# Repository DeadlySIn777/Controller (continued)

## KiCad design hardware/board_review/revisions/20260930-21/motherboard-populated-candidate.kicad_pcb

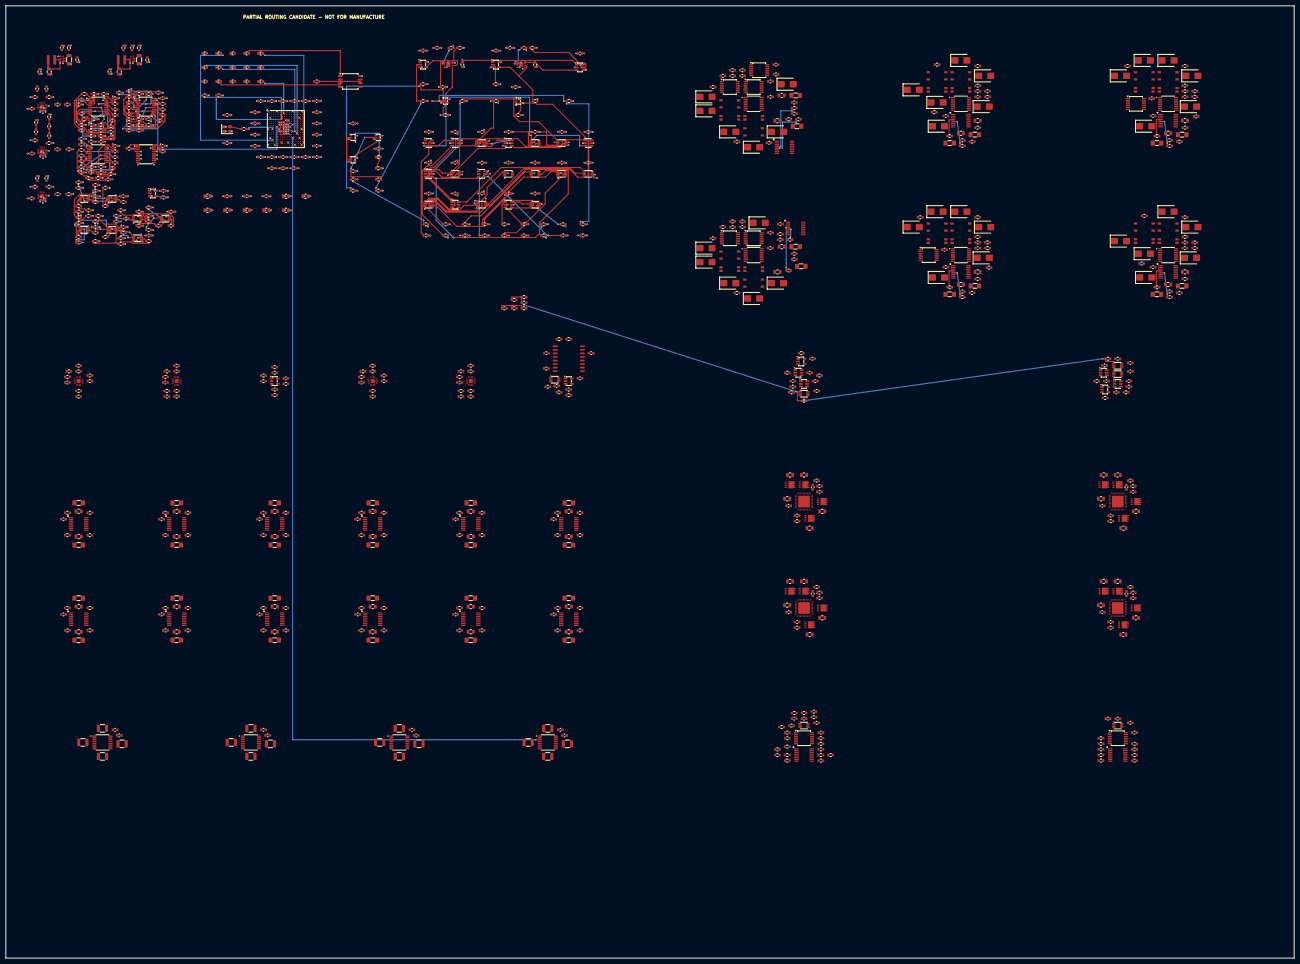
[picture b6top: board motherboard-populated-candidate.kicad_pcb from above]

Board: 6 copper layers, 460.0 x 340.0 mm, 880 parts (0 on the bottom side), 637 nets.

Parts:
C1001, C1002, C1003, C1004, C1005, C1006, C1007, C1008, C1009, C1010, C1011, C1012, C1013, C1014, C1015, C1016, C1017, C1018, C1019, C1020, C1021, C1022, C1023, C1035, C1038: 885012206046; C_0603_1608Metric
C1024, C1028, C1029, C1030, C1031, C1032, C1033, C1034: 885012207053; C_0805_2012Metric
C1025, C1026, C1027, C1036, C1039: 885012206052; C_0603_1608Metric
C1037: 885012206040; C_0603_1608Metric
C2001, C2004: C3216X7R1E106K160AB; C_1206_3216Metric
C2002, C2005: C2012X7S1A226M125AC; C_0805_2012Metric
C2003, C2006: GRM1885C1H682JA01D; C_0603_1608Metric
C2007, C2008, C2009, C2010, C3003, C3004, C3005, C3006, C3007, C3008, C3009, C4001, C4002, C4003, C4004, C4005, C4006, C4007, C4008, C4009, C4010, C4011, C4012, C4013, C4014, C4015, C4016, C4017, C4018, C4019, C5001, C5002, C5003, C5004, C5005, C5006, C5007, C5008, C5009, C5010, C5011: GRM188R72A104KA35D; C_0603_1608Metric
C3001, C3002: CL10C332JB8NNNC; C_0603_1608Metric
C6001, C6002, C6003, C6004, C6005, C6006, C6007, C6008, C6010, C6012, C6015, C6018, C6021, C6024, C6027, C6030, C6031, C6032, C6033, C6034, C6035, C6036, C6037, C6038, C6039, C6040, C6041, C6042: 100nF; C_0603_1608Metric
C6009, C6011: 1000nF; C_0603_1608Metric
C6013, C6014, C6016, C6017, C6019, C6020, C6022, C6023, C6025, C6026, C6028, C6029: 10nF; C_0805_2012Metric
C7001, C7003, C7005, C7007: 100nF 100V X7R; C_0603_1608Metric
C7002, C7004, C7006, C7008: 1uF 16V X7R; C_0603_1608Metric
C8001, C8002, C8003, C8004, C8005, C8006, C8007, C8008, C8009, C8010, C8011, C8012, C8013, C8014, C8015, C8016, C8017, C8018, C8019, C8020, C8021, C8022, C8023, C8024: 10nF 100V C0G; C_0805_2012Metric
C8101, C8102, C8103, C8104, C8105, C8106, C8107, C8108, C8109, C8110, C8111, C8112: 100nF 25V X7R; C_0603_1608Metric
C9001, C9002, C9003, C9004, C9005, C9006, C9007, C9008, C9009: 100nF 100V X7R 10%; C_0603_1608Metric
C10001, C10002, C10003, C10004, C10007, C10008, C10016, C10017, C10023, C10024, C10025, C10026, C10029, C10030, C10038, C10039: 100nF 100V; C_0603_1608Metric
C10005, C10014, C10027, C10036: 0.1nF 50V; C_0603_1608Metric
C10006, C10015, C10028, C10037: 2200nF 16V; C_0805_2012Metric
C10009, C10018, C10031, C10040: 1000nF 50V; C_0603_1608Metric
C10010, C10011, C10012, C10013, C10019, C10020, C10021, C10022, C10032, C10033, C10034, C10035, C10041, C10042, C10043, C10044: 22nF 100V; C_0805_2012Metric
D6001, D6002, D6003, D6004, D6005, D6006, D6007, D6008, D6009, D6010, D6011, D6012, D6013, D6014, D6015, D6016, D6017, D6018, D6019, D6020, D6021, D6022, D6023, D6024, D6025, D6026, D6027, D6028, D6029, D6030, D6031, D6032, D6033, D6034, D6035, D6036: SMBJ33CA 33V bidirectional; D_SMB
L2001: XGL4020-222MEC; XGL4020
L2002: XGL4020-102MEC; XGL4020
R1001, R1002, R5001, R5002, R5003, R5004, R5005, R5006, R5007, R5008, R5009, R5010, R5011, R5012, R5013, R5014, R5015, R5016, R5017, R5018, R5019, R5020, R5021, R5022, R5023, R5024, R5025, R5026, R5027, R5028, R5029, R5030, R5031, R5032, R5033, R5034, R5035, R5036, R5037, R5038: CRCW060333R0FKEA; R_0603_1608Metric
R1003, R1004, R1005, R1006, R1007, R1008, R1009, R1010, R1011, R1012, R1013, R1014, R1015, R1016, R1017, R1018, R1019, R1022, R1023, R1024, R1025, R2002, R2006, R2103, R2105, R3001, R3002, R4008, R4009, R4010, R4011, R4012, R4013, R4014, R4015, R4016, R4017, R4018, R5077, R5078, R5079, R5080, R5081, R5082, R5083, R5084, R5085, R5086, R5087, R5088, R5089, R5090, R5091, R5092, R5093, R5094, R5095, R5096, R5097, R5098, R5099, R5100, R5101, R5102: CRCW060310K0FKEA; R_0603_1608Metric
R1020, R2106: CRCW060347K0FKEA; R_0603_1608Metric
R1021: CRCW06031K00FKEA; R_0603_1608Metric
R2001: CRCW060376K8FKEA; R_0603_1608Metric
R2003, R2007, R3006, R3008, R3009, R3010, R3011, R3012: CRCW0603100KFKEA; R_0603_1608Metric
R2005: CRCW060332K4FKEA; R_0603_1608Metric
R2008: CRCW0603301KFKEA; R_0603_1608Metric
R2021: PLT0603Z8792LST1; R_0603_1608Metric
R2027, R2035, R2067, R2075: PLT0603Z1002LST1; R_0603_1608Metric
R2029: PLT0603Z9212LST1; R_0603_1608Metric
R2041: PLT0603Z1071LST1; R_0603_1608Metric
R2042: PLT0603Z2610LST1; R_0603_1608Metric
R2047, R2055: PLT0603Z1001LST1; R_0603_1608Metric
R2049: PLT0603Z1151LST1; R_0603_1608Metric
R2050: PLT0603Z3160LST1; R_0603_1608Metric
R2051: CRCW06034R02FKEA; R_0603_1608Metric
R2061: PLT0603Z5452LST1; R_0603_1608Metric
R2069: PLT0603Z5752LST1; R_0603_1608Metric
R2101, R2102: CRCW06033K30FKEA; R_0603_1608Metric
R2104: CRCW06036K80FKEA; R_0603_1608Metric
R2107: CRCW0603470KFKEA; R_0603_1608Metric
R2108, R3003, R3004, R3005, R3007, R3013, R4001, R4002, R4003, R4004, R4005, R4006, R4007, R5039, R5040, R5041, R5042, R5043, R5044, R5045, R5046, R5047, R5048, R5049, R5050, R5051, R5052, R5053, R5054, R5055, R5056, R5057, R5058, R5059, R5060, R5061, R5062, R5063, R5064, R5065, R5066, R5067, R5068, R5069, R5070, R5071, R5072, R5073, R5074, R5075, R5076: CRCW06034K70FKEA; R_0603_1608Metric
R6001, R6002, R6003, R6004, R6005, R6006, R6007, R6008, R6009, R6010, R6011, R6012, R6013, R6014, R6015, R6016, R6017, R6018, R6019, R6020, R6021, R6022, R6023, R6024, R6026, R6028, R6030, R6032, R6034, R6036, R6038, R6040, R6042, R6044, R6046, R6048, R6087, R6089, R6091, R6093, R10001, R10002, R10003, R10004, R10005, R10006, R10007, R10008, R10009, R10010, R10011, R10012, R10013, R10014, R10016, R10019, R10021, R10022, R10023, R10024, R10025, R10026, R10027, R10028, R10029, R10030, R10031, R10032, R10033, R10034, R10036, R10039: 10000R 1%; R_0603_1608Metric
R6025, R6027, R6029, R6031, R6033, R6035, R6037, R6039, R6041, R6043, R6045, R6047: 220R 1%; R_0603_1608Metric
R6049, R6050: 330R 1%; R_0603_1608Metric
R6051, R6054, R6057, R6060, R6063, R6066, R6069, R6072, R6075, R6078, R6081, R6084: 1000R 1%; R_MiniMELF_MMA-0204
R6052, R6055, R6058, R6061, R6064, R6067, R6070, R6073, R6076, R6079, R6082, R6085, R8101, R8102, R8103, R8104, R8105, R8106, R8107, R8108, R8109, R8110, R8111, R8112, R8113, R8114, R8115, R8116, R8117, R8118, R8119, R8120, R8121, R8122, R8123, R8124: 562R 1%; R_0603_1608Metric
R6053, R6056, R6059, R6062, R6065, R6068, R6071, R6074, R6077, R6080, R6083, R6086, R12005, R12006: 100000R 1%; R_0603_1608Metric
R6088, R6092: 60400R 1%; R_0603_1608Metric
R6090, R6094: 4700R 1%; R_0603_1608Metric
R6095, R6096, R10017, R10020, R10037, R10040: 1000R 1%; R_0603_1608Metric
R7001, R7002, R7003, R7004, R7005, R7006, R7007, R7008, R7009, R7010, R7011, R7012, R7013, R7014: 120R 1% 0.5W / FIT; R_1210_3225Metric
R7015, R7016: 120R 1% 0.5W / DNP; R_1210_3225Metric
R8001, R8002, R8003, R8004, R8005, R8006, R8007, R8008, R8009, R8010, R8011, R8012, R8013, R8014, R8015, R8016, R8017, R8018, R8019, R8020, R8021, R8022, R8023, R8024: 1k MELF 1%; R_MiniMELF_MMA-0204
R8201, R8202, R8203, R8204, R8205, R8206, R8207, R8208, R8209, R8210, R8211, R8212, R8213, R8214, R8215, R8216, R8217, R8218, R8219, R8220, R8221, R8222, R8223, R8224: 100k 1%; R_0603_1608Metric
R9001, R9011: 87900R 0.01% 5ppm; R_0603_1608Metric
R9002, R9004, R9006, R9008, R9012, R9014, R9016, R9018, R9022, R9024, R9026, R9028, R9032, R9034, R9036, R9038: 10000R 0.01% 5ppm; R_0603_1608Metric
R9003, R9013: 92100R 0.01% 5ppm; R_0603_1608Metric
R9005, R9015: 54500R 0.01% 5ppm; R_0603_1608Metric
R9007, R9017: 57500R 0.01% 5ppm; R_0603_1608Metric
R9009, R9019, R9029, R9039, R9041, R9042, R9043, R9044: 10000R 1% 100ppm; R_0603_1608Metric
R9010, R9020, R9030, R9040: 100000R 1% 100ppm; R_0603_1608Metric
R9021, R9031: 86700R 0.01% 5ppm; R_0603_1608Metric
R9023, R9033: 93100R 0.01% 5ppm; R_0603_1608Metric
R9025, R9035: 355000R 0.01% 5ppm; R_0603_1608Metric
R9027, R9037: 580000R 0.01% 5ppm; R_0603_1608Metric
R9045, R9046: 1000R 1% 100ppm; R_0603_1608Metric
R10015, R10035: 13300R 0.1%; R_0603_1608Metric
R10018, R10038: 17800R 0.1%; R_0603_1608Metric
R12001, R12002, R12003, R12004: 33R 1%; R_0603_1608Metric
U1001: T20F256I4; T20F256_Efinix_NSMD
U1002: W25Q32JVSSIQ; SOIC-8_5.3x5.3mm_P1.27mm
U1003, U1005, U3006, U3007: SN74LVC1G08DCKR; SOT-353_SC-70-5
U1004: 74LVC1G17GW; SOT-353_SC-70-5
U2001, U2002: TPS62901RPJR; TPS62901_RPJ9
U2003, U2004, U2005, U9001, U9002, U9003, U9004: LTC2962HUD#PBF; LTC2962_UD16
U2006, U9005, U9006: SN74LVC1G17DBVR; SOT-23-5
U3001, U3002: TPS3851G18SDRBT; TPS3851_DRB8
U3003, U3004: SN74LVC1G34DBVR; SOT-23-5
U3005: SN74LVC2G17DBVR; SOT-23-6
U4001, U4002, U4004, U4007, U4008, U4010: SN74LVC1G11DBVR; SOT-23-6
U4003, U4009, U4019, U6042, U9008: SN74LVC2G08DCUR; VSSOP-8_2.3x2mm_P0.5mm
U4005, U4006, U4011, U4012, U4013, U4014, U4015: SN74LVC2G74DCUR; VSSOP-8_2.3x2mm_P0.5mm
U4016, U4018: SN74LVC2G04DBVR; SOT-23-6
U4017: SN74LVC2G32DCUR; VSSOP-8_2.3x2mm_P0.5mm
U5001, U5002, U5003, U5004: SN74LVC244APWR; TSSOP-20_4.4x6.5mm_P0.65mm
U5005, U5006, U5007, U5008, U5009, U5010, U5011: SN74LVC2G126DCUR; VSSOP-8_2.3x2mm_P0.5mm
U6001, U6002, U6003, U6004, U6005, U6006: AM26C31IPWR; TSSOP-16_4.4x5mm_P0.65mm
U6007, U6008: 74LVC07APW,118; TSSOP-14_4.4x5mm_P0.65mm
U6009, U6011, U6013, U6015, U6017, U6019, U6021, U6023, U6025, U6027, U6029, U6031: TLP3640A(TPL,E; TLP3640A_SO4_11-3C1
U6010, U6012, U6014, U6016, U6018, U6020, U6022, U6024, U6026, U6028, U6030, U6032: TLP4176A(TP,F; TLP4176A_2.54SOP4_11-5H1S
U6033, U6034: TPS22918DBVR; SOT-23-6
U6035, U6036, U6037, U6038, U6039, U6040, U8001, U8002, U8003, U8004, U8005, U8006, U8007, U8008, U8009, U8010, U8011, U8012: ISO1212DBQR; ISO1212_DBQ16_TI
U6041, U6045: LTC6994IS6-2#TRPBF; TSOT-23-6
U6043, U6044, U10001, U10014: SN74LVC1G74DCUR; VSSOP-8_2.3x2mm_P0.5mm
U6046, U6047: 74LVC14APW,118; TSSOP-14_4.4x5mm_P0.65mm
U6048, U6049, U6050: SN74LVC00APWR; TSSOP-14_4.4x5mm_P0.65mm
U6051, U6052: 74AHCT1G17GVH; SOT-23-5
U7001, U7002, U7003, U7004: AM26LV32EIPWR; TSSOP-16_4.4x5mm_P0.65mm
U9007: ISO7720FDWR; ISO7720_DW16_TI_HV
U10002, U10015: SN74LVC08APWR; TSSOP-14_4.4x5mm_P0.65mm
U10003, U10016: ISO7762FDBQR; ISO7762_DBQ16_TI
U10004, U10009, U10017, U10022: TPS274C65ASRHAR; TPS274C65_RHA40_TI
U10005, U10006, U10007, U10008, U10010, U10011, U10012, U10013, U10018, U10019, U10020, U10021, U10023, U10024, U10025, U10026: CSD19538Q3AT; CSD19538_DNH8_TI
Y1001: ASE-50.000MHZ-L-C-T; Oscillator_SMD_Abracon_ASE-4Pin_3.2x2.5mm

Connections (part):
/BANK_B_BUFFER_ENABLE_QUALIFIED: R4014.1, R5076.1, U4013.6, U5005.1, U5005.7, U5006.1, U5006.7, U5007.1, U5007.7, U5008.1, U5008.7, U5009.1, U5009.7, U5010.1, U5010.7, U5011.1
/CORE_1V2: C1001.1, C1002.1, C1003.1, C1004.1, C1005.1, C1006.1, C1007.1, C1008.1, C1009.1, C1024.1, C1025.1, C1026.1, C1027.1, C2002.1, L2001.2, R2003.1, R2041.1, R2049.1, U1001.E9, U1001.F7, U1001.F8, U1001.F9, U1001.G11, U1001.J6, U1001.J7, U1001.K9, U1001.K11, U2001.3
/DIR0_FPGA: R5040.1, U1001.J5, U5001.4
/DIR1_FPGA: R5042.1, U1001.K3, U5001.11
/DIR2_FPGA: R5044.1, U1001.K1, U5001.17
/DIR3_FPGA: R5046.1, U1001.H1, U5002.6
/DIR4_FPGA: R5048.1, U1001.H2, U5002.13
/DIR5_FPGA: R5050.1, U1001.G3, U5003.2
/DIR6_FPGA: R5052.1, U1001.G2, U5003.8
/DIR7_FPGA: R5054.1, U1001.C1, U5003.15
/DIR8_FPGA: R5056.1, U1001.F3, U5005.5
/DIR9_FPGA: R5058.1, U1001.E1, U5007.2
/DIR10_FPGA: R5060.1, U1001.G4, U5008.5
/DIR11_FPGA: R5062.1, U1001.B1, U5010.2
/EN0_N_FPGA: R5063.1, U1001.H12, U5001.6
/EN1_N_FPGA: R5064.1, U1001.J12, U5001.13
/EN2_N_FPGA: R5065.1, U1001.L16, U5002.2
/EN3_N_FPGA: R5066.1, U1001.M15, U5002.8
/EN4_N_FPGA: R5067.1, U1001.M16, U5002.15
/EN5_N_FPGA: R5068.1, U1001.P16, U5003.4
/EN6_N_FPGA: R5069.1, U1001.L15, U5003.11
/EN7_N_FPGA: R5070.1, U1001.K12, U5003.17
/EN8_N_FPGA: R5071.1, U1001.N14, U5006.2
/EN9_N_FPGA: R5072.1, U1001.N16, U5007.5
/EN10_N_FPGA: R5073.1, U1001.P15, U5009.2
/EN11_N_FPGA: R5074.1, U1001.M14, U5010.5
/FPGA_CRESET_N: R2108.1, R4008.1, U1003.1, U2006.4, U4001.1, U4019.1, U4019.5
/FPGA_ENDPOINT_READY: R1023.1, R4001.1, U1001.C4, U4003.6, U4004.6
/FPGA_MOTION_REQUEST: R1024.1, R3003.1, U1001.B3, U3006.1, U4005.1, U4007.3
/FPGA_OUTPUT_REQUEST: R3004.1, U1001.K4, U3007.1, U4006.1, U4008.3
/FPGA_PROGRESS_M: R1025.1, R3005.1, U1001.E4, U3003.2
/FPGA_USER_RESET_N: R3013.1, R4009.1, U1001.D5, U1005.4, U3006.2, U3007.2, U4001.3
/IO_3V3: C1010.1, C1011.1, C1012.1, C1013.1, C1014.1, C1015.1, C1016.1, C1017.1, C1018.1, C1019.1, C1020.1, C1021.1, C1022.1, C1023.1, C1028.1, C1029.1, C1030.1, C1031.1, C1032.1, C1033.1, C1034.1, C1035.1, C1036.1, C1037.1, C1038.1, C2005.1, C2010.1, C3003.1, C3004.1, C3005.1, C3006.1, C3007.1, C3008.1, C3009.1, C4001.1, C4002.1, C4003.1, C4004.1, C4005.1, C4006.1, C4007.1, C4008.1, C4009.1, C4010.1, C4011.1, C4012.1, C4013.1, C4014.1, C4015.1, C4016.1, C4017.1, C4018.1, C4019.1, C5001.1, C5002.1, C5003.1, C5004.1, C5005.1, C5006.1, C5007.1, C5008.1, C5009.1, C5010.1, C5011.1, C6007.1, C6008.1, C6015.1, C6018.1, C6021.1, C6024.1, C6027.1, C6030.1, C6034.1, C6035.1, C6036.1, C6038.1, C6039.1, C6040.1, C6041.1, C6042.1, C7001.1, C7002.1, C7003.1, C7004.1, C7005.1, C7006.1, C7007.1, C7008.1, C8101.1, C8102.1, C8103.1, C8104.1, C8105.1, C8106.1, C8107.1, C8108.1, C8109.1, C8110.1, C8111.1, C8112.1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
/LOGIC_GND: C1001.2, C1002.2, C1003.2, C1004.2, C1005.2, C1006.2, C1007.2, C1008.2, C1009.2, C1010.2, C1011.2, C1012.2, C1013.2, C1014.2, C1015.2, C1016.2, C1017.2, C1018.2, C1019.2, C1020.2, C1021.2, C1022.2, C1023.2, C1024.2, C1025.2, C1026.2, C1027.2, C1028.2, C1029.2, C1030.2, C1031.2, C1032.2, C1033.2, C1034.2, C1035.2, C1036.2, C1037.2, C1038.2, C1039.2, C2001.2, C2002.2, C2003.2, C2004.2, C2005.2, C2006.2, C2007.2, C2008.2, C2009.2, C2010.2, C3001.2, C3002.2, C3003.2, C3004.2, C3005.2, C3006.2, C3007.2, C3008.2, C3009.2, C4001.2, C4002.2, C4003.2, C4004.2, C4005.2, C4006.2, C4007.2, C4008.2, C4009.2, C4010.2, C4011.2, C4012.2, C4013.2, C4014.2, C4015.2, C4016.2, C4017.2, C4018.2, C4019.2, C5001.2, C5002.2, C5003.2, C5004.2, C5005.2, C5006.2, C5007.2, C5008.2, C5009.2, C5010.2, C5011.2, C6001.2, C6002.2, C6003.2, C6004.2, C6005.2, C6006.2, C6007.2, C6008.2, C6009.2, C6010.2, C6011.2, C6012.2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
/RAW_INHIBIT_N: U1001.A2, U4003.5, U4003.7, U4007.6
/STEP0_FPGA: R5039.1, U1001.P2, U5001.2
/STEP1_FPGA: R5041.1, U1001.J4, U5001.8
/STEP2_FPGA: R5043.1, U1001.J3, U5001.15
/STEP3_FPGA: R5045.1, U1001.K2, U5002.4
/STEP4_FPGA: R5047.1, U1001.L1, U5002.11
/STEP5_FPGA: R5049.1, U1001.H4, U5002.17
/STEP6_FPGA: R5051.1, U1001.G5, U5003.6
/STEP7_FPGA: R5053.1, U1001.F1, U5003.13
/STEP8_FPGA: R5055.1, U1001.E2, U5005.2
/STEP9_FPGA: R5057.1, U1001.D1, U5006.5
/STEP10_FPGA: R5059.1, U1001.E3, U5008.2
/STEP11_FPGA: R5061.1, U1001.F4, U5009.5
/TX_PERMIT: R4015.1, R5075.1, U1001.E6, U4007.4, U4009.5, U4010.1, U4011.6, U5004.2, U5011.2
/WD_M_OK: R3009.1, U1001.T11, U3005.6, U4003.2, U4016.1
/WD_M_SET1_BUF: R3011.1, U3001.5, U3006.4, U4017.2
/WD_O_OK: R3010.1, U1001.M10, U3005.4, U4004.3, U4009.2, U4016.3
/WD_O_SET1_BUF: R3012.1, U3002.5, U3007.4, U4017.6
/fpga_core/ALM0_FPGA: R6053.1, U1001.B12, U6035.4
/fpga_core/ALM1_FPGA: R6056.1, U1001.B13, U6035.5
/fpga_core/ALM2_FPGA: R6059.1, U1001.B15, U6036.4
/fpga_core/ALM3_FPGA: R6062.1, U1001.C13, U6036.5
/fpga_core/ALM4_FPGA: R6065.1, U1001.C16, U6037.4
/fpga_core/ALM5_FPGA: R6068.1, U1001.E14, U6037.5
/fpga_core/ALM6_FPGA: R6071.1, U1001.F12, U6038.4
/fpga_core/ALM7_FPGA: R6074.1, U1001.D16, U6038.5
/fpga_core/ALM8_FPGA: R6077.1, U1001.G13, U6039.4
/fpga_core/ALM9_FPGA: R6080.1, U1001.F14, U6039.5
/fpga_core/ALM10_FPGA: R6083.1, U1001.E16, U6040.4
/fpga_core/ALM11_FPGA: R6086.1, U1001.E15, U6040.5
/fpga_core/ENC0_A_FPGA: U1001.B5, U7001.3
/fpga_core/ENC0_B_FPGA: U1001.A7, U7001.5
/fpga_core/ENC0_Z_FPGA: U1001.B7, U7001.11
/fpga_core/ENC1_A_FPGA: U1001.B6, U7001.13
/fpga_core/ENC1_B_FPGA: U1001.A6, U7002.3
/fpga_core/ENC1_Z_FPGA: U1001.E7, U7002.5
/fpga_core/ENC2_A_FPGA: U1001.D9, U7002.11
/fpga_core/ENC2_B_FPGA: U1001.E8, U7002.13
/fpga_core/ENC2_Z_FPGA: U1001.C9, U7003.3
/fpga_core/ENC3_A_FPGA: U1001.D10, U7003.5
/fpga_core/ENC3_B_FPGA: U1001.B9, U7003.11
/fpga_core/ENC3_Z_FPGA: U1001.C10, U7003.13
/fpga_core/FPGA_CDONE: R1003.2, R1022.1, U1001.R1
/fpga_core/FPGA_CFG_CBSEL0: R1018.1, U1001.C7
/fpga_core/FPGA_CFG_CBSEL1: R1019.1, U1001.D7
/fpga_core/FPGA_CFG_CBUS0: R1009.2, U1001.K13
/fpga_core/FPGA_CFG_CBUS1: R1008.2, U1001.L14
/fpga_core/FPGA_CFG_CBUS2: R1007.2, U1001.R16
/fpga_core/FPGA_CFG_CSI: R1004.2, U1001.N3
/fpga_core/FPGA_CFG_NSTATUS: R1017.2, U1001.B8
/fpga_core/FPGA_CFG_TEST_N: R1005.2, U1001.L12
/fpga_core/FPGA_CLK_50M: R1001.2, U1001.H3
/fpga_core/FPGA_CLK_SOURCE: R1001.1, Y1001.3
/fpga_core/FPGA_FLASH_CCK: R1002.2, U1002.6
/fpga_core/FPGA_FLASH_CCK_SOURCE: R1002.1, U1001.M3
/fpga_core/FPGA_FLASH_CS_N: R1006.2, U1001.P3, U1002.1
/fpga_core/FPGA_FLASH_IO2: R1014.2, U1002.3
/fpga_core/FPGA_FLASH_IO3: R1015.2, U1002.7
/fpga_core/FPGA_FLASH_MISO: U1001.N1, U1002.2
/fpga_core/FPGA_FLASH_MOSI: U1001.L3, U1002.5
/fpga_core/FPGA_JTAG_TCK: R1010.2, U1001.M2
/fpga_core/FPGA_JTAG_TDI: R1011.2, U1001.K5
/fpga_core/FPGA_JTAG_TDO: R1013.2, U1001.L5
/fpga_core/FPGA_JTAG_TMS: R1012.2, U1001.M1
/fpga_core/FPGA_LOCAL_RESET_N: R1020.2, R1021.1, U1001.P1, U1003.4
/fpga_core/FPGA_SERVICE_RUN_N: R1016.2, U1003.2, U1005.2
/fpga_core/FPGA_USER_RESET_DELAYED: U1004.4, U1005.1
/fpga_core/FPGA_USER_RESET_RC: C1039.1, R1022.2, U1004.2
/fpga_core/FREQ0_FPGA: U1001.M12, U7004.3
/fpga_core/FREQ1_FPGA: U1001.R9, U7004.5
/fpga_core/MPG_A_FPGA: U1001.T10, U7004.11
/fpga_core/MPG_B_FPGA: U1001.N10, U7004.13
/fpga_core/OPI_REARM_M: R6090.1, R6094.1, R12001.1, R12002.1, R12005.1, U1001.J2, U6043.1, U6044.1
/fpga_core/WATCHDOG_TRIP_CLEAR: R12003.1, R12004.1, R12006.1, U1001.D6
/mc_local_power/CORE_1V2_EN: R2002.1, R2102.2, R2103.1, U2001.5
/mc_local_power/CORE_1V2_MODE: R2001.1, U2001.7
/mc_local_power/CORE_1V2_OV_SENSE: R2051.2, R2055.1, U2004.15
/mc_local_power/CORE_1V2_SS: C2003.1, U2001.8
/mc_local_power/CORE_1V2_SW: L2001.1, U2001.2
/mc_local_power/CORE_1V2_UV_SENSE: R2042.2, R2047.1, U2004.16
/mc_local_power/CORE_5V: C2001.1, C2004.1, C2007.1, C2008.1, C2009.1, R2021.1, R2029.1, R2101.1, R2104.1, R2106.1, U2001.6, U2002.6, U2003.1, U2003.2, U2003.4, U2003.10, U2003.13, U2003.14, U2004.1, U2004.4, U2004.10, U2004.13, U2004.14, U2005.1, U2005.4, U2005.10, U2005.13, U2005.14
/mc_local_power/CORE_5V_OV_SENSE: R2029.2, R2035.1, U2003.15
/mc_local_power/CORE_5V_UV_SENSE: R2021.2, R2027.1, U2003.16
/mc_local_power/IO_3V3_EN: R2006.1, R2104.2, R2105.1, U2002.5, U2004.12, U2005.2
/mc_local_power/IO_3V3_MODE: R2005.1, U2002.7
/mc_local_power/IO_3V3_OV_SENSE: R2069.2, R2075.1, U2005.15
/mc_local_power/IO_3V3_SS: C2006.1, U2002.8
/mc_local_power/IO_3V3_SW: L2002.1, U2002.2
/mc_local_power/IO_3V3_UV_SENSE: R2061.2, R2067.1, U2005.16
/mc_local_power/IO_3V3_VSET: R2008.1, U2002.9
/mc_local_power/MC_RAILS_OK_5V: R2106.2, R2107.1, U2005.12, U2006.2
/mc_local_power/MC_SEQ_5V_OK: R2101.2, R2102.1, U2003.12, U2004.2
/mc_local_power/MC_SEQ_OV2_1: R2049.2, R2050.1
/mc_local_power/MC_SEQ_OV2_2: R2050.2, R2051.1
/mc_local_power/MC_SEQ_REF1: U2003.5, U2003.6, U2003.8, U2003.9
/mc_local_power/MC_SEQ_REF2: U2004.5, U2004.6, U2004.8, U2004.9
/mc_local_power/MC_SEQ_REF3: U2005.5, U2005.6, U2005.8, U2005.9
/mc_local_power/MC_SEQ_UV2_1: R2041.2, R2042.1
/mc_motor_buffers/DIR0_BUFFER_OUT: R5002.1, U5001.16
/mc_motor_buffers/DIR0_TO_MIA: R5002.2, R5078.1, R6002.1, U6001.7
/mc_motor_buffers/DIR1_BUFFER_OUT: R5005.1, U5001.9
/mc_motor_buffers/DIR1_TO_MIA: R5005.2, R5080.1, R6004.1, U6001.15
/mc_motor_buffers/DIR2_BUFFER_OUT: R5008.1, U5001.3
/mc_motor_buffers/DIR2_TO_MIA: R5008.2, R5082.1, R6006.1, U6002.7
/mc_motor_buffers/DIR3_BUFFER_OUT: R5011.1, U5002.14
/mc_motor_buffers/DIR3_TO_MIA: R5011.2, R5084.1, R6008.1, U6002.15
/mc_motor_buffers/DIR4_BUFFER_OUT: R5014.1, U5002.7
/mc_motor_buffers/DIR4_TO_MIA: R5014.2, R5086.1, R6010.1, U6003.7
/mc_motor_buffers/DIR5_BUFFER_OUT: R5017.1, U5003.18
/mc_motor_buffers/DIR5_TO_MIA: R5017.2, R5088.1, R6012.1, U6003.15
/mc_motor_buffers/DIR6_BUFFER_OUT: R5020.1, U5003.12
/mc_motor_buffers/DIR6_TO_MIA: R5020.2, R5090.1, R6014.1, U6004.7
/mc_motor_buffers/DIR7_BUFFER_OUT: R5023.1, U5003.5
/mc_motor_buffers/DIR7_TO_MIA: R5023.2, R5092.1, R6016.1, U6004.15
/mc_motor_buffers/DIR8_BUFFER_OUT: R5026.1, U5005.3
/mc_motor_buffers/DIR8_TO_MX4: R5026.2, R5094.1, R6018.1, U6005.7
/mc_motor_buffers/DIR9_BUFFER_OUT: R5029.1, U5007.6
/mc_motor_buffers/DIR9_TO_MX4: R5029.2, R5096.1, R6020.1, U6005.15
/mc_motor_buffers/DIR10_BUFFER_OUT: R5032.1, U5008.3
/mc_motor_buffers/DIR10_TO_MX4: R5032.2, R5098.1, R6022.1, U6006.7
/mc_motor_buffers/DIR11_BUFFER_OUT: R5035.1, U5010.6
/mc_motor_buffers/DIR11_TO_MX4: R5035.2, R5100.1, R6024.1, U6006.15
/mc_motor_buffers/EN0_N_BUFFER_OUT: R5003.1, U5001.14
/mc_motor_buffers/EN0_N_TO_MIA: R5003.2, R6026.1, U6046.1
/mc_motor_buffers/EN1_N_BUFFER_OUT: R5006.1, U5001.7
/mc_motor_buffers/EN1_N_TO_MIA: R5006.2, R6028.1, U6046.3
/mc_motor_buffers/EN2_N_BUFFER_OUT: R5009.1, U5002.18
/mc_motor_buffers/EN2_N_TO_MIA: R5009.2, R6030.1, U6046.5
/mc_motor_buffers/EN3_N_BUFFER_OUT: R5012.1, U5002.12
/mc_motor_buffers/EN3_N_TO_MIA: R5012.2, R6032.1, U6046.9
/mc_motor_buffers/EN4_N_BUFFER_OUT: R5015.1, U5002.5
/mc_motor_buffers/EN4_N_TO_MIA: R5015.2, R6034.1, U6046.11
/mc_motor_buffers/EN5_N_BUFFER_OUT: R5018.1, U5003.16
/mc_motor_buffers/EN5_N_TO_MIA: R5018.2, R6036.1, U6046.13
/mc_motor_buffers/EN6_N_BUFFER_OUT: R5021.1, U5003.9
/mc_motor_buffers/EN6_N_TO_MIA: R5021.2, R6038.1, U6047.1
/mc_motor_buffers/EN7_N_BUFFER_OUT: R5024.1, U5003.3
/mc_motor_buffers/EN7_N_TO_MIA: R5024.2, R6040.1, U6047.3
/mc_motor_buffers/EN8_N_BUFFER_OUT: R5027.1, U5006.6
/mc_motor_buffers/EN8_N_TO_MX4: R5027.2, R6042.1, U6047.5
/mc_motor_buffers/EN9_N_BUFFER_OUT: R5030.1, U5007.3
/mc_motor_buffers/EN9_N_TO_MX4: R5030.2, R6044.1, U6047.9
/mc_motor_buffers/EN10_N_BUFFER_OUT: R5033.1, U5009.6
/mc_motor_buffers/EN10_N_TO_MX4: R5033.2, R6046.1, U6047.11
/mc_motor_buffers/EN11_N_BUFFER_OUT: R5036.1, U5010.3
/mc_motor_buffers/EN11_N_TO_MX4: R5036.2, R6048.1, U6047.13
/mc_motor_buffers/STEP0_BUFFER_OUT: R5001.1, U5001.18
/mc_motor_buffers/STEP0_TO_MIA: R5001.2, R5077.1, R6001.1, U6001.1
/mc_motor_buffers/STEP1_BUFFER_OUT: R5004.1, U5001.12
/mc_motor_buffers/STEP1_TO_MIA: R5004.2, R5079.1, R6003.1, U6001.9
/mc_motor_buffers/STEP2_BUFFER_OUT: R5007.1, U5001.5
/mc_motor_buffers/STEP2_TO_MIA: R5007.2, R5081.1, R6005.1, U6002.1
/mc_motor_buffers/STEP3_BUFFER_OUT: R5010.1, U5002.16
/mc_motor_buffers/STEP3_TO_MIA: R5010.2, R5083.1, R6007.1, U6002.9
/mc_motor_buffers/STEP4_BUFFER_OUT: R5013.1, U5002.9
/mc_motor_buffers/STEP4_TO_MIA: R5013.2, R5085.1, R6009.1, U6003.1
/mc_motor_buffers/STEP5_BUFFER_OUT: R5016.1, U5002.3
/mc_motor_buffers/STEP5_TO_MIA: R5016.2, R5087.1, R6011.1, U6003.9
/mc_motor_buffers/STEP6_BUFFER_OUT: R5019.1, U5003.14
/mc_motor_buffers/STEP6_TO_MIA: R5019.2, R5089.1, R6013.1, U6004.1
/mc_motor_buffers/STEP7_BUFFER_OUT: R5022.1, U5003.7
/mc_motor_buffers/STEP7_TO_MIA: R5022.2, R5091.1, R6015.1, U6004.9
/mc_motor_buffers/STEP8_BUFFER_OUT: R5025.1, U5005.6
/mc_motor_buffers/STEP8_TO_MX4: R5025.2, R5093.1, R6017.1, U6005.1
/mc_motor_buffers/STEP9_BUFFER_OUT: R5028.1, U5006.3
/mc_motor_buffers/STEP9_TO_MX4: R5028.2, R5095.1, R6019.1, U6005.9
/mc_motor_buffers/STEP10_BUFFER_OUT: R5031.1, U5008.6
/mc_motor_buffers/STEP10_TO_MX4: R5031.2, R5097.1, R6021.1, U6006.1
/mc_motor_buffers/STEP11_BUFFER_OUT: R5034.1, U5009.3
/mc_motor_buffers/STEP11_TO_MX4: R5034.2, R5099.1, R6023.1, U6006.9
/mc_motor_buffers/TX_PERMIT_A_BUFFER_OUT: R5037.1, U5004.18
/mc_motor_buffers/TX_PERMIT_A_TO_MIA: R5037.2, R5101.1, R6087.1, U6051.2
/mc_motor_buffers/TX_PERMIT_B_BUFFER_OUT: R5038.1, U5011.6
/mc_motor_buffers/TX_PERMIT_B_TO_MX4: R5038.2, R5102.1, R6091.1, U6052.2
/mc_permission/ARM_M_Q: U4005.5, U4007.1
/mc_permission/ARM_O_Q: U4006.5, U4008.1
/mc_permission/BASE_FIRST: U4001.4, U4002.1
/mc_permission/BASE_OK: U4002.4, U4003.1, U4004.1, U4009.1
/mc_permission/DIC_OK_QUALIFIED: R4010.1, U4001.6
/mc_permission/EXT_PERMIT_3V3: R4011.1, U4002.3
/mc_permission/LATCH_CLEAR_M_N: U4003.3, U4005.6
/mc_permission/LATCH_CLEAR_O_N: U4004.4, U4006.6
/mc_permission/OPI_OK_BOE: U1001.P11, U4013.5
/mc_permission/OPI_OK_OUT: U1001.R12, U4012.5
/mc_permission/OPI_OK_TX: U1001.P13, U4011.5
/mc_permission/OPI_REARM_BOE: R4004.1, R12002.2, U4013.1
/mc_permission/OPI_REARM_OUT: R4003.1, U1001.H5, U4012.1
/mc_permission/OPI_REARM_TX: R4002.1, R12001.2, U4011.1
/mc_permission/OUTPUT_RAW_OK: U4008.6, U4009.7
/mc_permission/OUT_PERMIT: R4016.1, R10001.1, R10021.1, U1001.R14, U4008.4, U4010.3, U4012.6, U10002.1, U10002.4, U10015.1, U10015.4
/mc_permission/PERMIT_OUT_DRIVE: R4018.1, U4009.3
/mc_permission/PERMIT_OUT_REQ: R4007.1, U1001.F5, U4009.6
/mc_permission/PROCESS_PERMIT_EXT_3V3: R4013.1, U4010.6
/mc_permission/PROC_PERMIT: R4017.1, U1001.R15, U4010.4
/mc_permission/TAMPER_CLEAR_N: R4012.1, U1001.R4, U4002.6
/mc_permission/WD_M_FALL_CLK: U4014.1, U4016.6
/mc_permission/WD_M_RECORD_CLEAR_N: U4018.6, U4019.2
/mc_permission/WD_M_TRIP_CLEAR_N: U4014.6, U4019.7
/mc_permission/WD_M_TRIP_D: U4014.2, U4017.7
/mc_permission/WD_M_TRIP_N: U1001.T9, U4014.3
/mc_permission/WD_M_TRIP_Q: U4014.5, U4017.1
/mc_permission/WD_O_FALL_CLK: U4015.1, U4016.4
/mc_permission/WD_O_RECORD_CLEAR_N: U4018.4, U4019.6
/mc_permission/WD_O_TRIP_CLEAR_N: U4015.6, U4019.3
/mc_permission/WD_O_TRIP_D: U4015.2, U4017.3
/mc_permission/WD_O_TRIP_N: U1001.P10, U4015.3
/mc_permission/WD_O_TRIP_Q: U4015.5, U4017.5
/mc_permission/WD_REARM_M: R4005.1, R12003.2, U4018.1
/mc_permission/WD_REARM_O: R4006.1, R12004.2, U4018.3
/motherboard_di/DI0_IN: R8101.2, U8001.15
/motherboard_di/DI0_LOGIC: R8201.1, U8001.4
/motherboard_di/DI0_SENSE: C8001.1, R8001.2, R8101.1, U8001.16
/motherboard_di/DI1_IN: R8102.2, U8001.10
/motherboard_di/DI1_LOGIC: R8202.1, U8001.5
/motherboard_di/DI1_SENSE: C8002.1, R8002.2, R8102.1, U8001.11
/motherboard_di/DI2_IN: R8103.2, U8002.15
/motherboard_di/DI2_LOGIC: R8203.1, U8002.4
/motherboard_di/DI2_SENSE: C8003.1, R8003.2, R8103.1, U8002.16
/motherboard_di/DI3_IN: R8104.2, U8002.10
/motherboard_di/DI3_LOGIC: R8204.1, U8002.5
/motherboard_di/DI3_SENSE: C8004.1, R8004.2, R8104.1, U8002.11
/motherboard_di/DI4_IN: R8105.2, U8003.15
/motherboard_di/DI4_LOGIC: R8205.1, U8003.4
/motherboard_di/DI4_SENSE: C8005.1, R8005.2, R8105.1, U8003.16
/motherboard_di/DI5_IN: R8106.2, U8003.10
/motherboard_di/DI5_LOGIC: R8206.1, U8003.5
/motherboard_di/DI5_SENSE: C8006.1, R8006.2, R8106.1, U8003.11
/motherboard_di/DI6_IN: R8107.2, U8004.15
/motherboard_di/DI6_LOGIC: R8207.1, U8004.4
/motherboard_di/DI6_SENSE: C8007.1, R8007.2, R8107.1, U8004.16
/motherboard_di/DI7_IN: R8108.2, U8004.10
/motherboard_di/DI7_LOGIC: R8208.1, U8004.5
/motherboard_di/DI7_SENSE: C8008.1, R8008.2, R8108.1, U8004.11
/motherboard_di/DI8_IN: R8109.2, U8005.15
/motherboard_di/DI8_LOGIC: R8209.1, U8005.4
/motherboard_di/DI8_SENSE: C8009.1, R8009.2, R8109.1, U8005.16
/motherboard_di/DI9_IN: R8110.2, U8005.10
/motherboard_di/DI9_LOGIC: R8210.1, U8005.5
/motherboard_di/DI9_SENSE: C8010.1, R8010.2, R8110.1, U8005.11
/motherboard_di/DI10_IN: R8111.2, U8006.15
/motherboard_di/DI10_LOGIC: R8211.1, U8006.4
/motherboard_di/DI10_SENSE: C8011.1, R8011.2, R8111.1, U8006.16
/motherboard_di/DI11_IN: R8112.2, U8006.10
/motherboard_di/DI11_LOGIC: R8212.1, U8006.5
/motherboard_di/DI11_SENSE: C8012.1, R8012.2, R8112.1, U8006.11
/motherboard_di/DI12_IN: R8113.2, U8007.15
/motherboard_di/DI12_LOGIC: R8213.1, U8007.4
/motherboard_di/DI12_SENSE: C8013.1, R8013.2, R8113.1, U8007.16
/motherboard_di/DI13_IN: R8114.2, U8007.10
/motherboard_di/DI13_LOGIC: R8214.1, U8007.5
/motherboard_di/DI13_SENSE: C8014.1, R8014.2, R8114.1, U8007.11
/motherboard_di/DI14_IN: R8115.2, U8008.15
/motherboard_di/DI14_LOGIC: R8215.1, U8008.4
/motherboard_di/DI14_SENSE: C8015.1, R8015.2, R8115.1, U8008.16
/motherboard_di/DI15_IN: R8116.2, U8008.10
/motherboard_di/DI15_LOGIC: R8216.1, U8008.5
/motherboard_di/DI15_SENSE: C8016.1, R8016.2, R8116.1, U8008.11
/motherboard_di/DI16_IN: R8117.2, U8009.15
/motherboard_di/DI16_LOGIC: R8217.1, U8009.4
/motherboard_di/DI16_SENSE: C8017.1, R8017.2, R8117.1, U8009.16
/motherboard_di/DI17_IN: R8118.2, U8009.10
/motherboard_di/DI17_LOGIC: R8218.1, U8009.5
/motherboard_di/DI17_SENSE: C8018.1, R8018.2, R8118.1, U8009.11
/motherboard_di/DI18_IN: R8119.2, U8010.15
/motherboard_di/DI18_LOGIC: R8219.1, U8010.4
/motherboard_di/DI18_SENSE: C8019.1, R8019.2, R8119.1, U8010.16
/motherboard_di/DI19_IN: R8120.2, U8010.10
/motherboard_di/DI19_LOGIC: R8220.1, U8010.5
/motherboard_di/DI19_SENSE: C8020.1, R8020.2, R8120.1, U8010.11
/motherboard_di/DI20_IN: R8121.2, U8011.15
/motherboard_di/DI20_LOGIC: R8221.1, U8011.4
/motherboard_di/DI20_SENSE: C8021.1, R8021.2, R8121.1, U8011.16
/motherboard_di/DI21_IN: R8122.2, U8011.10
/motherboard_di/DI21_LOGIC: R8222.1, U8011.5
/motherboard_di/DI21_SENSE: C8022.1, R8022.2, R8122.1, U8011.11
/motherboard_di/DI22_IN: R8123.2, U8012.15
/motherboard_di/DI22_LOGIC: R8223.1, U8012.4
/motherboard_di/DI22_SENSE: C8023.1, R8023.2, R8123.1, U8012.16
/motherboard_di/DI23_IN: R8124.2, U8012.10
/motherboard_di/DI23_LOGIC: R8224.1, U8012.5
/motherboard_di/DI23_SENSE: C8024.1, R8024.2, R8124.1, U8012.11
/motherboard_di/FIELD_B_0V: C8001.2, C8002.2, C8003.2, C8004.2, C8005.2, C8006.2, C8007.2, C8008.2, C8009.2, C8010.2, C8011.2, C8012.2, C8013.2, C8014.2, C8015.2, C8016.2, C8017.2, C8018.2, C8019.2, C8020.2, C8021.2, C8022.2, C8023.2, C8024.2, U8001.9, U8001.14, U8002.9, U8002.14, U8003.9, U8003.14, U8004.9, U8004.14, U8005.9, U8005.14, U8006.9, U8006.14, U8007.9, U8007.14, U8008.9, U8008.14, U8009.9, U8009.14, U8010.9, U8010.14, U8011.9, U8011.14, U8012.9, U8012.14
/motherboard_do/DO00: C10010.1, U10005.5, U10005.6, U10005.7, U10005.8, U10005.9
/motherboard_do/DO00_RCB_GATE: U10004.40, U10005.4
/motherboard_do/DO00_SW: U10004.38, U10004.39, U10005.1, U10005.2, U10005.3
/motherboard_do/DO01: C10011.1, U10006.5, U10006.6, U10006.7, U10006.8, U10006.9
/motherboard_do/DO01_RCB_GATE: U10004.31, U10006.4
/motherboard_do/DO01_SW: U10004.32, U10004.33, U10006.1, U10006.2, U10006.3
/motherboard_do/DO02: C10012.1, U10007.5, U10007.6, U10007.7, U10007.8, U10007.9
/motherboard_do/DO02_RCB_GATE: U10004.11, U10007.4
/motherboard_do/DO02_SW: U10004.12, U10004.13, U10007.1, U10007.2, U10007.3
/motherboard_do/DO03: C10013.1, U10008.5, U10008.6, U10008.7, U10008.8, U10008.9
/motherboard_do/DO03_RCB_GATE: U10004.20, U10008.4
/motherboard_do/DO03_SW: U10004.18, U10004.19, U10008.1, U10008.2, U10008.3
/motherboard_do/DO04: C10019.1, U10010.5, U10010.6, U10010.7, U10010.8, U10010.9
/motherboard_do/DO04_RCB_GATE: U10009.40, U10010.4
/motherboard_do/DO04_SW: U10009.38, U10009.39, U10010.1, U10010.2, U10010.3
/motherboard_do/DO05: C10020.1, U10011.5, U10011.6, U10011.7, U10011.8, U10011.9
/motherboard_do/DO05_RCB_GATE: U10009.31, U10011.4
/motherboard_do/DO05_SW: U10009.32, U10009.33, U10011.1, U10011.2, U10011.3
/motherboard_do/DO06: C10021.1, U10012.5, U10012.6, U10012.7, U10012.8, U10012.9
/motherboard_do/DO06_RCB_GATE: U10009.11, U10012.4
/motherboard_do/DO06_SW: U10009.12, U10009.13, U10012.1, U10012.2, U10012.3
/motherboard_do/DO07: C10022.1, U10013.5, U10013.6, U10013.7, U10013.8, U10013.9
/motherboard_do/DO07_RCB_GATE: U10009.20, U10013.4
/motherboard_do/DO07_SW: U10009.18, U10009.19, U10013.1, U10013.2, U10013.3
/motherboard_do/DO08: C10032.1, U10018.5, U10018.6, U10018.7, U10018.8, U10018.9
/motherboard_do/DO08_RCB_GATE: U10017.40, U10018.4
/motherboard_do/DO08_SW: U10017.38, U10017.39, U10018.1, U10018.2, U10018.3
/motherboard_do/DO09: C10033.1, U10019.5, U10019.6, U10019.7, U10019.8, U10019.9
/motherboard_do/DO09_RCB_GATE: U10017.31, U10019.4
/motherboard_do/DO09_SW: U10017.32, U10017.33, U10019.1, U10019.2, U10019.3
/motherboard_do/DO10: C10034.1, U10020.5, U10020.6, U10020.7, U10020.8, U10020.9
/motherboard_do/DO10_RCB_GATE: U10017.11, U10020.4
/motherboard_do/DO10_SW: U10017.12, U10017.13, U10020.1, U10020.2, U10020.3
/motherboard_do/DO11: C10035.1, U10021.5, U10021.6, U10021.7, U10021.8, U10021.9
/motherboard_do/DO11_RCB_GATE: U10017.20, U10021.4
/motherboard_do/DO11_SW: U10017.18, U10017.19, U10021.1, U10021.2, U10021.3
/motherboard_do/DO12: C10041.1, U10023.5, U10023.6, U10023.7, U10023.8, U10023.9
/motherboard_do/DO12_RCB_GATE: U10022.40, U10023.4
/motherboard_do/DO12_SW: U10022.38, U10022.39, U10023.1, U10023.2, U10023.3
/motherboard_do/DO13: C10042.1, U10024.5, U10024.6, U10024.7, U10024.8, U10024.9
/motherboard_do/DO13_RCB_GATE: U10022.31, U10024.4
/motherboard_do/DO13_SW: U10022.32, U10022.33, U10024.1, U10024.2, U10024.3
/motherboard_do/DO14: C10043.1, U10025.5, U10025.6, U10025.7, U10025.8, U10025.9
/motherboard_do/DO14_RCB_GATE: U10022.11, U10025.4
/motherboard_do/DO14_SW: U10022.12, U10022.13, U10025.1, U10025.2, U10025.3
/motherboard_do/DO15: C10044.1, U10026.5, U10026.6, U10026.7, U10026.8, U10026.9
/motherboard_do/DO15_RCB_GATE: U10022.20, U10026.4
/motherboard_do/DO15_SW: U10022.18, U10022.19, U10026.1, U10026.2, U10026.3
/motherboard_do/DOA_CARD_EN: R10004.1, U10002.10
/motherboard_do/DOA_CLR_N: U10001.6, U10002.3
/motherboard_do/DOA_CONTROLLER_RESET_N: R10002.1, U10002.2
/motherboard_do/DOA_CS_N_FIELD: R10012.1, U10003.13, U10004.10, U10009.10
/motherboard_do/DOA_CS_N_HOST: R10008.1, U10003.4
/motherboard_do/DOA_DO_EN_FIELD: R10009.1, U10003.12, U10004.3, U10009.3
/motherboard_do/DOA_DO_EN_LOGIC: R10005.1, U10002.8, U10003.5
/motherboard_do/DOA_FIELD_3V3: C10004.1, C10006.1, C10007.1, C10015.1, C10016.1, R10012.2, R10014.2, U10003.16, U10004.4, U10009.4
/motherboard_do/DOA_FLT_N_FIELD: R10014.1, U10003.10, U10004.2, U10009.2
/motherboard_do/DOA_IO_ENABLE_STROBE: R10003.1, U10001.1
/motherboard_do/DOA_OUT_EN_LATCH: U10001.5, U10002.5
/motherboard_do/DOA_PERMIT_LATCHED: U10002.6, U10002.9
/motherboard_do/DOA_Q0_ADDRESS: R10015.1, U10004.30
/motherboard_do/DOA_Q0_ISNS: C10005.1, R10017.1, U10004.6
/motherboard_do/DOA_Q0_READY_N: R10016.1, U10004.1
/motherboard_do/DOA_Q1_ADDRESS: R10018.1, U10009.30
/motherboard_do/DOA_Q1_ISNS: C10014.1, R10020.1, U10009.6
/motherboard_do/DOA_Q1_READY_N: R10019.1, U10009.1
/motherboard_do/DOA_SCLK_FIELD: R10010.1, U10003.15, U10004.9, U10009.9
/motherboard_do/DOA_SCLK_HOST: R10006.1, U10003.2
/motherboard_do/DOA_SDI_FIELD: R10011.1, U10003.14, U10004.8, U10009.8
/motherboard_do/DOA_SDI_HOST: R10007.1, U10003.3
/motherboard_do/DOA_SDO_FIELD: R10013.1, U10003.11, U10004.7, U10009.7
/motherboard_do/DOB_CARD_EN: R10024.1, U10015.10
/motherboard_do/DOB_CLR_N: U10014.6, U10015.3
/motherboard_do/DOB_CONTROLLER_RESET_N: R10022.1, U10015.2
/motherboard_do/DOB_CS_N_FIELD: R10032.1, U10016.13, U10017.10, U10022.10
/motherboard_do/DOB_CS_N_HOST: R10028.1, U10016.4
/motherboard_do/DOB_DO_EN_FIELD: R10029.1, U10016.12, U10017.3, U10022.3
/motherboard_do/DOB_DO_EN_LOGIC: R10025.1, U10015.8, U10016.5
/motherboard_do/DOB_FIELD_3V3: C10026.1, C10028.1, C10029.1, C10037.1, C10038.1, R10032.2, R10034.2, U10016.16, U10017.4, U10022.4
/motherboard_do/DOB_FLT_N_FIELD: R10034.1, U10016.10, U10017.2, U10022.2
/motherboard_do/DOB_IO_ENABLE_STROBE: R10023.1, U10014.1
/motherboard_do/DOB_OUT_EN_LATCH: U10014.5, U10015.5
/motherboard_do/DOB_PERMIT_LATCHED: U10015.6, U10015.9
/motherboard_do/DOB_Q0_ADDRESS: R10035.1, U10017.30
/motherboard_do/DOB_Q0_ISNS: C10027.1, R10037.1, U10017.6
/motherboard_do/DOB_Q0_READY_N: R10036.1, U10017.1
/motherboard_do/DOB_Q1_ADDRESS: R10038.1, U10022.30
/motherboard_do/DOB_Q1_ISNS: C10036.1, R10040.1, U10022.6
/motherboard_do/DOB_Q1_READY_N: R10039.1, U10022.1
/motherboard_do/DOB_SCLK_FIELD: R10030.1, U10016.15, U10017.9, U10022.9
/motherboard_do/DOB_SCLK_HOST: R10026.1, U10016.2
/motherboard_do/DOB_SDI_FIELD: R10031.1, U10016.14, U10017.8, U10022.8
/motherboard_do/DOB_SDI_HOST: R10027.1, U10016.3
/motherboard_do/DOB_SDO_FIELD: R10033.1, U10016.11, U10017.7, U10022.7
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
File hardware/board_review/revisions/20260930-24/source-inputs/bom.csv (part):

Reference,Value,MPN,Footprint,Status,DNP,Scope
U1001,T20F256I4 / CANDIDATE PIN ALLOCATION,T20F256I4,CNC_Motion:T20F256_Efinix_NSMD,candidate_not_qualified,false,actual_on_motherboard_component_candidate
U1002,W25Q32JVSSIQ / x1 SPI,W25Q32JVSSIQ,Package_SO:SOIC-8_5.3x5.3mm_P1.27mm,candidate_not_qualified,false,actual_on_motherboard_component_candidate
Y1001,ASE-50.000MHZ-L-C-T,ASE-50.000MHZ-L-C-T,Oscillator:Oscillator_SMD_Abracon_ASE-4Pin_3.2x2.5mm,candidate_not_qualified,false,actual_on_motherboard_component_candidate
U1003,SN74LVC1G08DCKR / RESET AND,SN74LVC1G08DCKR,Package_TO_SOT_SMD:SOT-353_SC-70-5,candidate_not_qualified,false,actual_on_motherboard_component_candidate
U1004,74LVC1G17GW / CDONE DELAY SCHMITT,74LVC1G17GW,Package_TO_SOT_SMD:SOT-353_SC-70-5,candidate_not_qualified,false,actual_on_motherboard_component_candidate
U1005,SN74LVC1G08DCKR / USER RESET AND,SN74LVC1G08DCKR,Package_TO_SOT_SMD:SOT-353_SC-70-5,candidate_not_qualified,false,actual_on_motherboard_component_candidate
R1001,33R 1%,CRCW060333R0FKEA,Resistor_SMD:R_0603_1608Metric,candidate_not_qualified,false,actual_on_motherboard_component_candidate
R1002,33R 1%,CRCW060333R0FKEA,Resistor_SMD:R_0603_1608Metric,candidate_not_qualified,false,actual_on_motherboard_component_candidate
R1003,10000R 1%,CRCW060310K0FKEA,Resistor_SMD:R_0603_1608Metric,candidate_not_qualified,false,actual_on_motherboard_component_candidate
R1004,10000R 1%,CRCW060310K0FKEA,Resistor_SMD:R_0603_1608Metric,candidate_not_qualified,false,actual_on_motherboard_component_candidate
R1005,10000R 1%,CRCW060310K0FKEA,Resistor_SMD:R_0603_1608Metric,candidate_not_qualified,false,actual_on_motherboard_component_candidate
R1006,10000R 1%,CRCW060310K0FKEA,Resistor_SMD:R_0603_1608Metric,candidate_not_qualified,false,actual_on_motherboard_component_candidate
R1007,10000R 1%,CRCW060310K0FKEA,Resistor_SMD:R_0603_1608Metric,candidate_not_qualified,false,actual_on_motherboard_component_candidate
R1008,10000R 1%,CRCW060310K0FKEA,Resistor_SMD:R_0603_1608Metric,candidate_not_qualified,false,actual_on_motherboard_component_candidate
R1009,10000R 1%,CRCW060310K0FKEA,Resistor_SMD:R_0603_1608Metric,candidate_not_qualified,false,actual_on_motherboard_component_candidate
R1010,10000R 1%,CRCW060310K0FKEA,Resistor_SMD:R_0603_1608Metric,candidate_not_qualified,false,actual_on_motherboard_component_candidate
R1011,10000R 1%,CRCW060310K0FKEA,Resistor_SMD:R_0603_1608Metric,candidate_not_qualified,false,actual_on_motherboard_component_candidate
R1012,10000R 1%,CRCW060310K0FKEA,Resistor_SMD:R_0603_1608Metric,candidate_not_qualified,false,actual_on_motherboard_component_candidate
R1013,10000R 1%,CRCW060310K0FKEA,Resistor_SMD:R_0603_1608Metric,candidate_not_qualified,false,actual_on_motherboard_component_candidate
R1014,10000R 1%,CRCW060310K0FKEA,Resistor_SMD:R_0603_1608Metric,candidate_not_qualified,false,actual_on_motherboard_component_candidate
R1015,10000R 1%,CRCW060310K0FKEA,Resistor_SMD:R_0603_1608Metric,candidate_not_qualified,false,actual_on_motherboard_component_candidate
R1016,10000R 1%,CRCW060310K0FKEA,Resistor_SMD:R_0603_1608Metric,candidate_not_qualified,false,actual_on_motherboard_component_candidate
R1017,10000R 1%,CRCW060310K0FKEA,Resistor_SMD:R_0603_1608Metric,candidate_not_qualified,false,actual_on_motherboard_component_candidate
R1018,10000R 1%,CRCW060310K0FKEA,Resistor_SMD:R_0603_1608Metric,candidate_not_qualified,false,actual_on_motherboard_component_candidate
R1019,10000R 1%,CRCW060310K0FKEA,Resistor_SMD:R_0603_1608Metric,candidate_not_qualified,false,actual_on_motherboard_component_candidate
R1020,47000R 1%,CRCW060347K0FKEA,Resistor_SMD:R_0603_1608Metric,candidate_not_qualified,false,actual_on_motherboard_component_candidate
R1021,1000R 1%,CRCW06031K00FKEA,Resistor_SMD:R_0603_1608Metric,candidate_not_qualified,false,actual_on_motherboard_component_candidate
R1022,10000R 1%,CRCW060310K0FKEA,Resistor_SMD:R_0603_1608Metric,candidate_not_qualified,false,actual_on_motherboard_component_candidate
R1023,10000R 1%,CRCW060310K0FKEA,Resistor_SMD:R_0603_1608Metric,candidate_not_qualified,false,actual_on_motherboard_component_candidate
R1024,10000R 1%,CRCW060310K0FKEA,Resistor_SMD:R_0603_1608Metric,candidate_not_qualified,false,actual_on_motherboard_component_candidate
R1025,10000R 1%,CRCW060310K0FKEA,Resistor_SMD:R_0603_1608Metric,candidate_not_qualified,false,actual_on_motherboard_component_candidate
C1001,0.1uF 16V X7R,885012206046,Capacitor_SMD:C_0603_1608Metric,candidate_not_qualified,false,actual_on_motherboard_component_candidate
C1002,0.1uF 16V X7R,885012206046,Capacitor_SMD:C_0603_1608Metric,candidate_not_qualified,false,actual_on_motherboard_component_candidate
C1003,0.1uF 16V X7R,885012206046,Capacitor_SMD:C_0603_1608Metric,candidate_not_qualified,false,actual_on_motherboard_component_candidate
C1004,0.1uF 16V X7R,885012206046,Capacitor_SMD:C_0603_1608Metric,candidate_not_qualified,false,actual_on_motherboard_component_candidate
C1005,0.1uF 16V X7R,885012206046,Capacitor_SMD:C_0603_1608Metric,candidate_not_qualified,false,actual_on_motherboard_component_candidate
C1006,0.1uF 16V X7R,885012206046,Capacitor_SMD:C_0603_1608Metric,candidate_not_qualified,false,actual_on_motherboard_component_candidate
C1007,0.1uF 16V X7R,885012206046,Capacitor_SMD:C_0603_1608Metric,candidate_not_qualified,false,actual_on_motherboard_component_candidate
C1008,0.1uF 16V X7R,885012206046,Capacitor_SMD:C_0603_1608Metric,candidate_not_qualified,false,actual_on_motherboard_component_candidate
C1009,0.1uF 16V X7R,885012206046,Capacitor_SMD:C_0603_1608Metric,candidate_not_qualified,false,actual_on_motherboard_component_candidate
C1010,0.1uF 16V X7R,885012206046,Capacitor_SMD:C_0603_1608Metric,candidate_not_qualified,false,actual_on_motherboard_component_candidate
C1011,0.1uF 16V X7R,885012206046,Capacitor_SMD:C_0603_1608Metric,candidate_not_qualified,false,actual_on_motherboard_component_candidate
C1012,0.1uF 16V X7R,885012206046,Capacitor_SMD:C_0603_1608Metric,candidate_not_qualified,false,actual_on_motherboard_component_candidate
C1013,0.1uF 16V X7R,885012206046,Capacitor_SMD:C_0603_1608Metric,candidate_not_qualified,false,actual_on_motherboard_component_candidate
C1014,0.1uF 16V X7R,885012206046,Capacitor_SMD:C_0603_1608Metric,candidate_not_qualified,false,actual_on_motherboard_component_candidate
C1015,0.1uF 16V X7R,885012206046,Capacitor_SMD:C_0603_1608Metric,candidate_not_qualified,false,actual_on_motherboard_component_candidate
C1016,0.1uF 16V X7R,885012206046,Capacitor_SMD:C_0603_1608Metric,candidate_not_qualified,false,actual_on_motherboard_component_candidate
C1017,0.1uF 16V X7R,885012206046,Capacitor_SMD:C_0603_1608Metric,candidate_not_qualified,false,actual_on_motherboard_component_candidate
C1018,0.1uF 16V X7R,885012206046,Capacitor_SMD:C_0603_1608Metric,candidate_not_qualified,false,actual_on_motherboard_component_candidate
C1019,0.1uF 16V X7R,885012206046,Capacitor_SMD:C_0603_1608Metric,candidate_not_qualified,false,actual_on_motherboard_component_candidate
C1020,0.1uF 16V X7R,885012206046,Capacitor_SMD:C_0603_1608Metric,candidate_not_qualified,false,actual_on_motherboard_component_candidate
C1021,0.1uF 16V X7R,885012206046,Capacitor_SMD:C_0603_1608Metric,candidate_not_qualified,false,actual_on_motherboard_component_candidate
C1022,0.1uF 16V X7R,885012206046,Capacitor_SMD:C_0603_1608Metric,candidate_not_qualified,false,actual_on_motherboard_component_candidate
C1023,0.1uF 16V X7R,885012206046,Capacitor_SMD:C_0603_1608Metric,candidate_not_qualified,false,actual_on_motherboard_component_candidate
C1024,4.7uF 16V X7R,885012207053,Capacitor_SMD:C_0805_2012Metric,candidate_not_qualified,false,actual_on_motherboard_component_candidate
C1025,1uF 16V X7R,885012206052,Capacitor_SMD:C_0603_1608Metric,candidate_not_qualified,false,actual_on_motherboard_component_candidate
C1026,1uF 16V X7R,885012206052,Capacitor_SMD:C_0603_1608Metric,candidate_not_qualified,false,actual_on_motherboard_component_candidate
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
